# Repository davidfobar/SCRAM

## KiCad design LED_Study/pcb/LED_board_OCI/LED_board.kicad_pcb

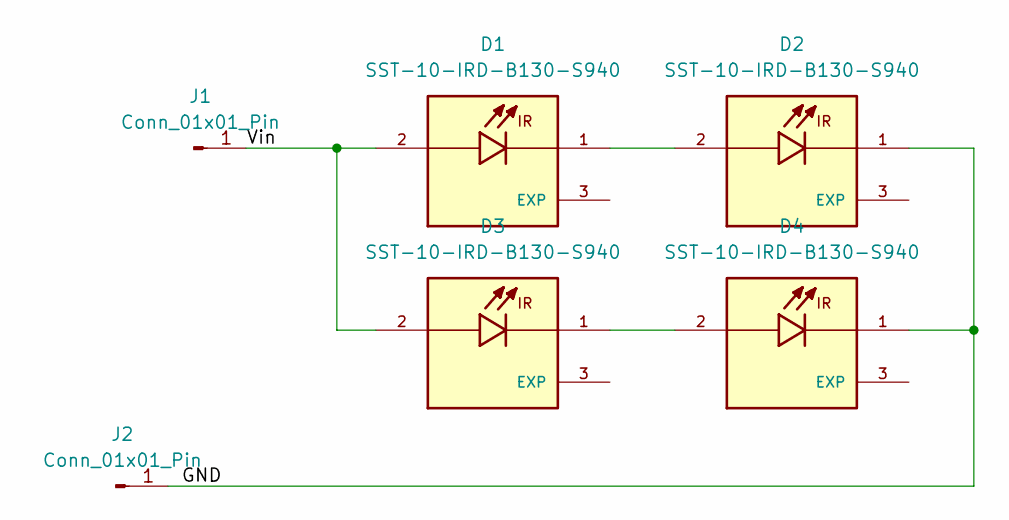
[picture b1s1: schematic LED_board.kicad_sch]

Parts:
D1, D2, D3, D4: SST-10-IRD-B130-S940; OCI-490; PARTREV 01
J1, J2: Conn_01x01_Pin; PinHeader_1x01_P1.00mm_Vertical

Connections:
/GND: D2.1, D4.1, J2.1
/Vin: D1.2, D3.2, J1.1
unnamed: D1.1, D2.2
unnamed: D3.1, D4.2

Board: 2 copper layers, 6 parts (0 on the bottom side), 4 nets, no tracks yet.

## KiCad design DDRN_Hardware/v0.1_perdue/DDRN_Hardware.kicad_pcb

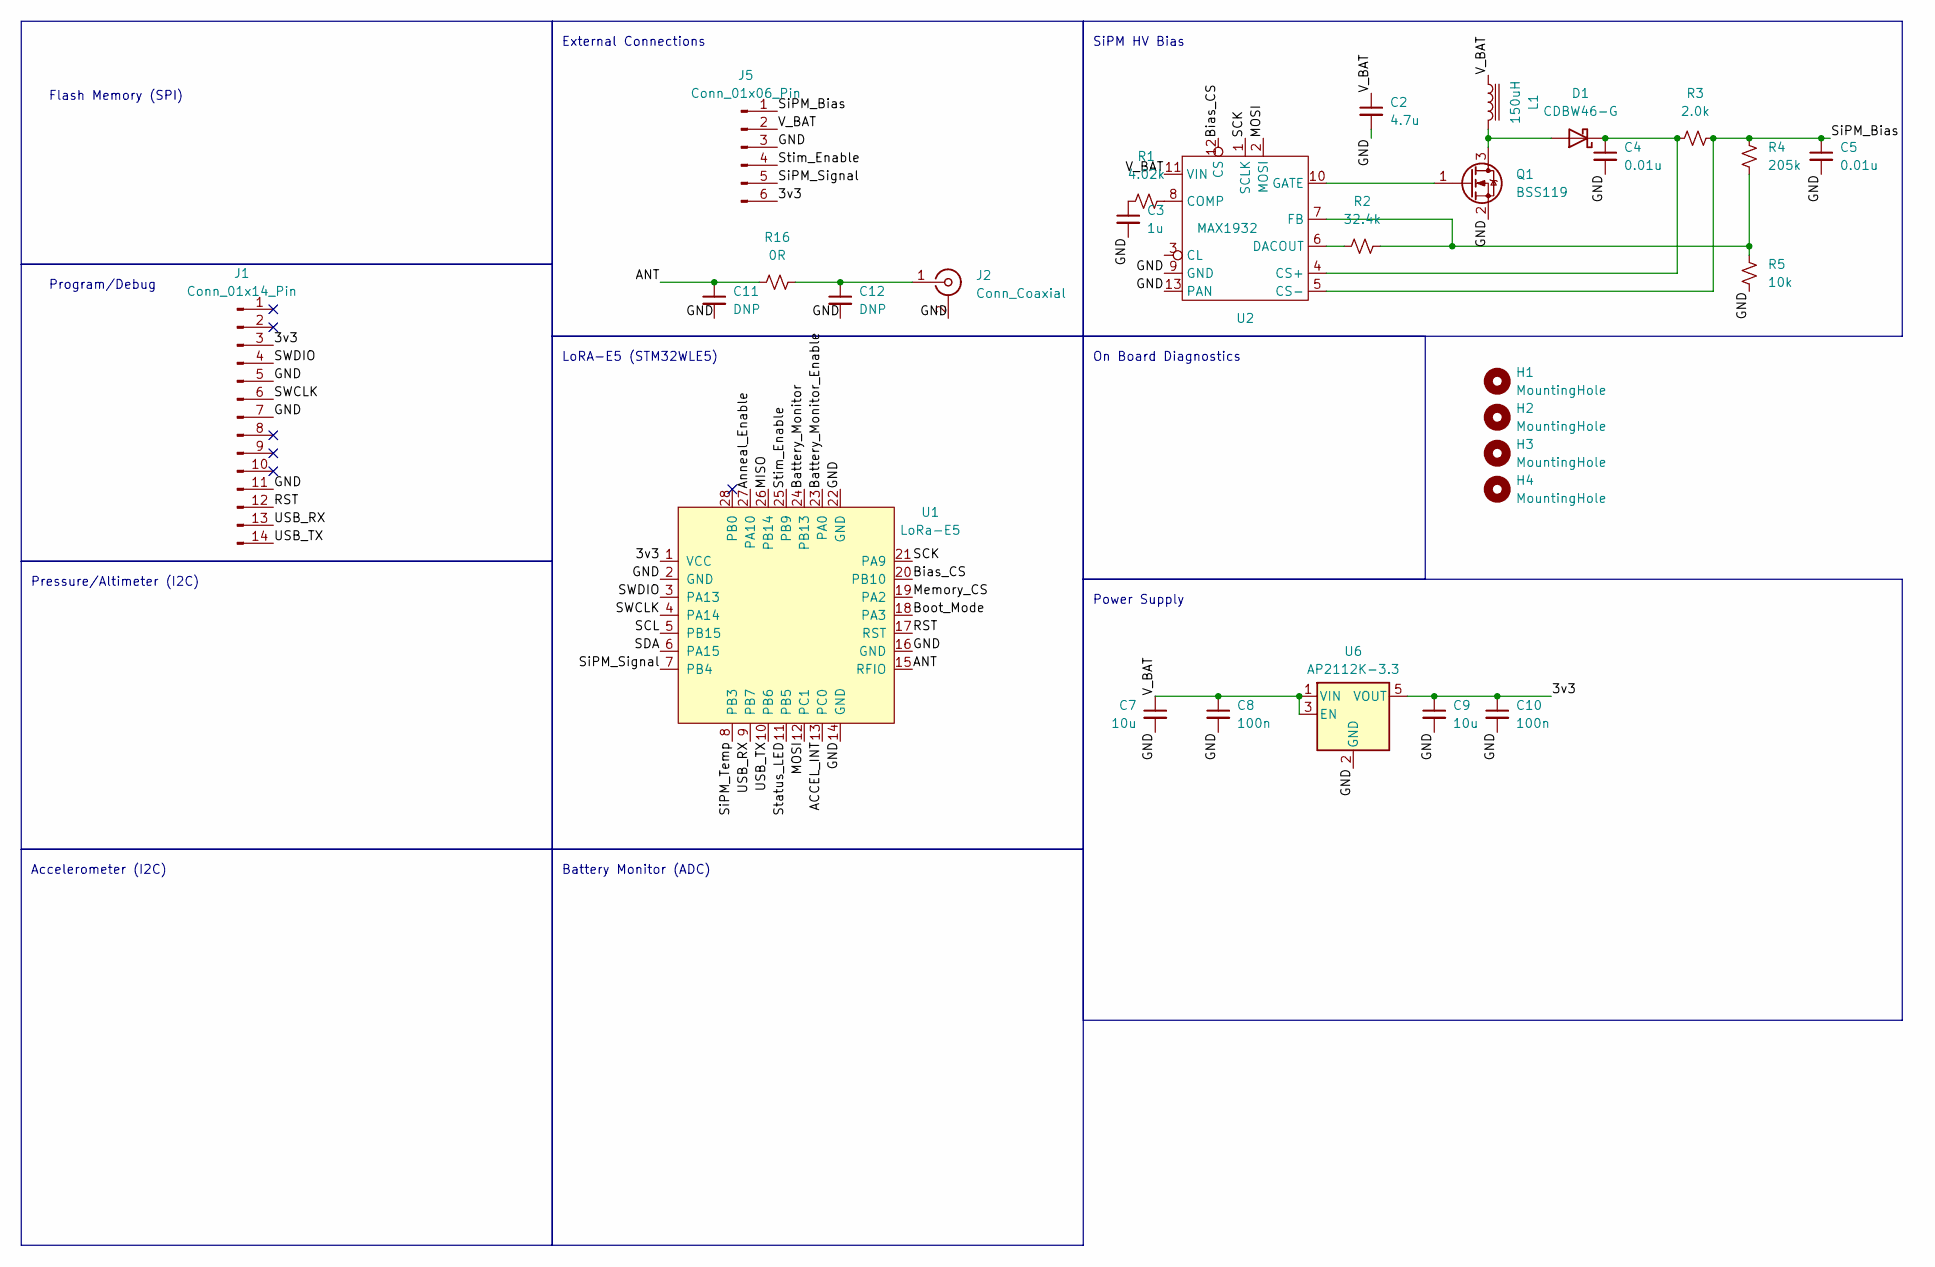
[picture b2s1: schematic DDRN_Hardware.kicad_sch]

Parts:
C2: 4.7u; C_0805_2012Metric_Pad1.18x1.45mm_HandSolder
C3: 1u; C_0805_2012Metric_Pad1.18x1.45mm_HandSolder
C4, C5: 0.01u; C_0805_2012Metric_Pad1.18x1.45mm_HandSolder
C7, C9: 10u; C_0805_2012Metric_Pad1.18x1.45mm_HandSolder
C8, C10: 100n; C_0805_2012Metric_Pad1.18x1.45mm_HandSolder
C11, C12: DNP; C_0805_2012Metric_Pad1.18x1.45mm_HandSolder
D1: CDBW46-G; D_SOD-123
H1, H2, H3, H4: MountingHole; MountingHole_3.2mm_M3_DIN965
J1: Conn_01x14_Pin; Tag-Connect_TC2070-IDC-FP_2x07_P1.27mm_Vertical
J2: Conn_Coaxial; U.FL_Hirose_U.FL-R-SMT-1_Vertical
J5: Conn_01x06_Pin; Tag-Connect_TC2030-IDC-FP_2x03_P1.27mm_Vertical
L1: 150uH; SRN4026
Q1: BSS119; SOT-23
R1: 4.02k; R_0805_2012Metric_Pad1.20x1.40mm_HandSolder
R2: 32.4k; R_0805_2012Metric_Pad1.20x1.40mm_HandSolder
R3: 2.0k; R_0805_2012Metric_Pad1.20x1.40mm_HandSolder
R4: 205k; R_0805_2012Metric_Pad1.20x1.40mm_HandSolder
R5: 10k; R_0805_2012Metric_Pad1.20x1.40mm_HandSolder
R16: 0R; R_0805_2012Metric_Pad1.20x1.40mm_HandSolder
U1: LoRa-E5
U2: MAX1932; MAX1932_handsolder
U6: AP2112K-3.3; SOT-23-5

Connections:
/3v3: C9.1, C10.1, J1.3, J5.6, U1.1 (VCC), U6.5 (VOUT)
/ACCEL_INT: U1.13 (PC0)
/ANT: C11.1, R16.2, U1.15 (RFIO)
/Anneal_Enable: U1.27 (PA10)
/Battery_Monitor: U1.24 (PB13~)
/Battery_Monitor_Enable: U1.23 (PA0)
/Bias_CS: U1.20 (PB10), U2.12 (CS)
/Boot_Mode: U1.18 (PA3)
/GND: C2.2, C3.2, C4.2, C5.2, C7.2, C8.2, C9.2, C10.2, C11.2, C12.2, J1.5, J1.7, J1.11, J2.2 (Ext), J5.3, Q1.2 (S), R5.2, U1.2 (GND), U1.14 (GND), U1.16 (GND), U1.22 (GND), U2.9 (GND), U2.13 (PAN), U6.2 (GND)
/MISO: U1.26 (PB14)
/MOSI: U1.12 (PC1), U2.2 (MOSI)
/Memory_CS: U1.19 (PA2)
/RST: J1.12, U1.17 (RST)
/SCK: U1.21 (PA9), U2.1 (SCLK)
/SCL: U1.5 (PB15)
/SDA: U1.6 (PA15)
/SWCLK: J1.6, U1.4 (PA14)
/SWDIO: J1.4, U1.3 (PA13)
/SiPM_Bias: C5.1, J5.1, R3.2, R4.1, U2.5 (CS-)
/SiPM_Signal: J5.5, U1.7 (PB4)
/SiPM_Temp: U1.8 (PB3)
/Status_LED: U1.11 (PB5)
/Stim_Enable: J5.4, U1.25 (PB9)
/USB_RX: J1.13, U1.9 (PB7)
/USB_TX: J1.14, U1.10 (PB6)
/V_BAT: C2.1, C7.1, C8.1, J5.2, L1.1, U2.11 (VIN), U6.1 (VIN), U6.3 (EN)
unnamed: C3.1, R1.1
unnamed: D1.2 (A), L1.2, Q1.3 (D)
unnamed: C4.1, D1.1 (K), R3.1, U2.4 (CS+)
unnamed: C12.1, J2.1 (In), R16.1
unnamed: Q1.1 (G), U2.10 (GATE)
unnamed: R1.2, U2.8 (COMP)
unnamed: R2.1, U2.6 (DACOUT)
unnamed: R2.2, R4.2, R5.1, U2.7 (FB)

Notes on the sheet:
Power Supply
Pressure/Altimeter (I2C)
Accelerometer (I2C)
On Board Diagnostics
Flash Memory (SPI)
External Connections
SiPM HV Bias
Program/Debug
LoRA-E5 (STM32WLE5)
Battery Monitor (ADC)

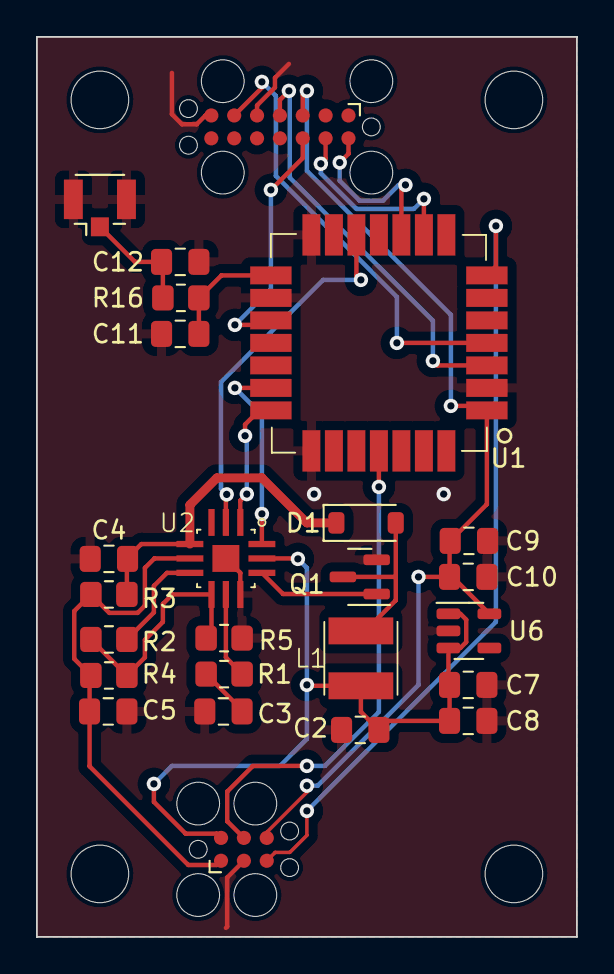
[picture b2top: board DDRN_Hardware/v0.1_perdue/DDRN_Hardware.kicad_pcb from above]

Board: 2 copper layers, 30.0 x 50.0 mm, 29 parts (0 on the bottom side), 23 nets.

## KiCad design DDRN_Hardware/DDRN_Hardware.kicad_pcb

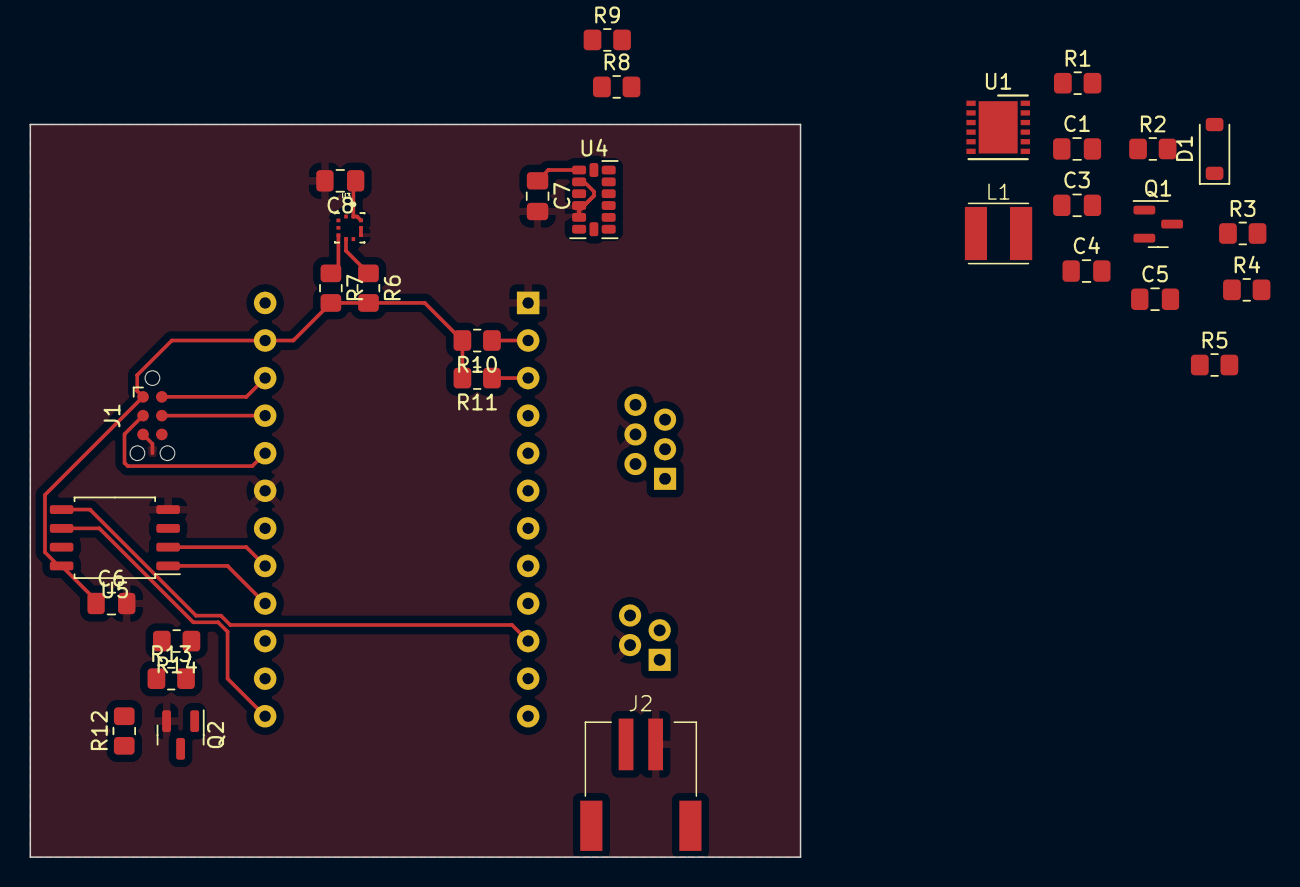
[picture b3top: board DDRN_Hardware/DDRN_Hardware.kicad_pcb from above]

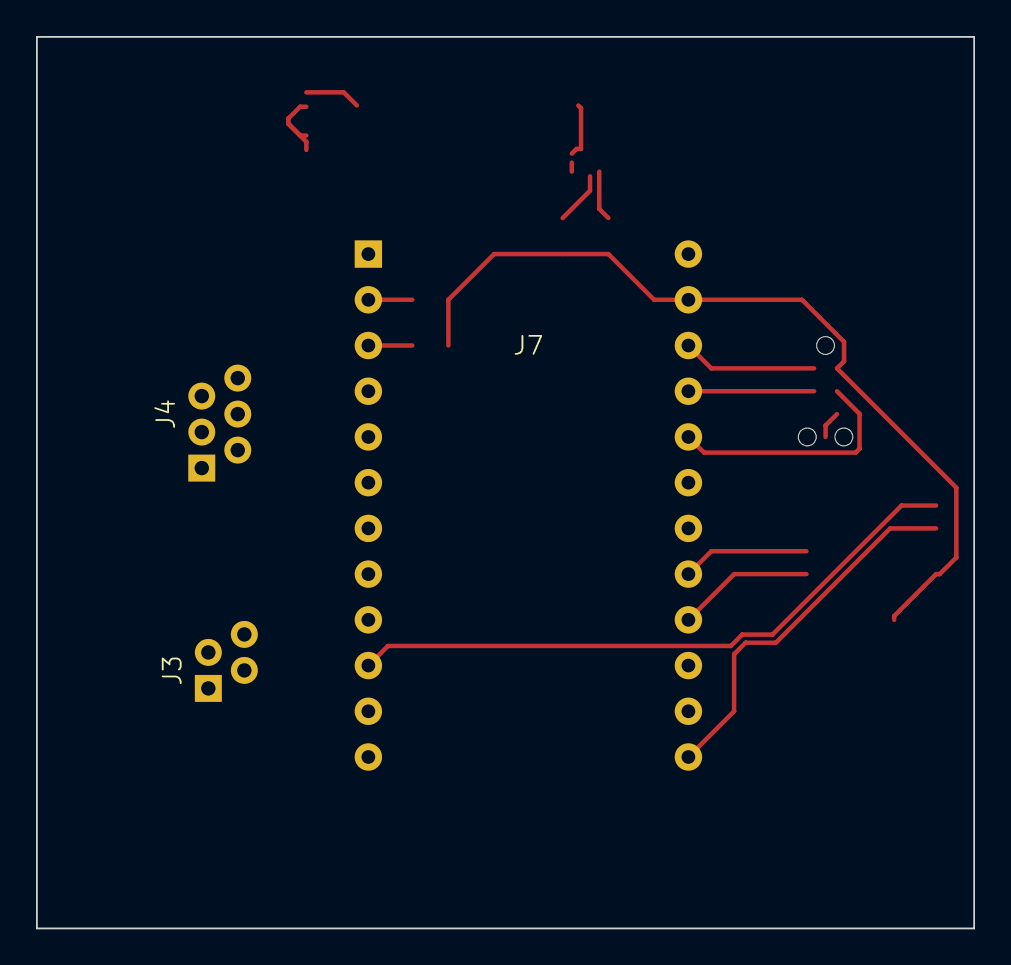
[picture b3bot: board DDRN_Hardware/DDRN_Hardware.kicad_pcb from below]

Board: 2 copper layers, 52.1 x 49.5 mm, 34 parts (3 on the bottom side), 34 nets.

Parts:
C1: 4.7u; C_0805_2012Metric_Pad1.18x1.45mm_HandSolder
C3, C6, C7, C8: 1u; C_0805_2012Metric_Pad1.18x1.45mm_HandSolder
C4, C5: 0.01u; C_0805_2012Metric_Pad1.18x1.45mm_HandSolder
D1: CDBW46-G; D_SOD-123
J1: SWD; Tag-Connect_TC2030-IDC-NL_2x03_P1.27mm_Vertical
J2: Conn_01x02_Pin; JST-PH-RH-SM
J3: Conn_01x04_Pin; SLW4S-1C7LF
J4: Conn_01x06_Pin; SLW6S-1C7LF
J7: Conn_02x12_Counter_Clockwise; E5-mini-dev
L1: 150uH; SRN4026
Q1, Q2: BSS119; SOT-23
R1: 4.02k; R_0805_2012Metric_Pad1.20x1.40mm_HandSolder
R2: 32.4k; R_0805_2012Metric_Pad1.20x1.40mm_HandSolder
R3: 2.0k; R_0805_2012Metric_Pad1.20x1.40mm_HandSolder
R4: 205k; R_0805_2012Metric_Pad1.20x1.40mm_HandSolder
R5, R6, R7, R8, R9, R12, R13: 10k; R_0805_2012Metric_Pad1.20x1.40mm_HandSolder
R10, R11: 4.7k; R_0805_2012Metric_Pad1.20x1.40mm_HandSolder
R14: 100; R_0805_2012Metric_Pad1.20x1.40mm_HandSolder
U1: MAX1932; DFN-12-1EP_4x4mm_P0.65mm_EP2.64x3.54mm
U3: BMP390L; XDCR_BMP390L
U4: ADXL343; LGA-14_3x5mm_P0.8mm_LayoutBorder1x6y
U5: W25Q32JVSS; SOIC-8_5.23x5.23mm_P1.27mm

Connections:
/3v3: C1.1, C6.1, C7.1, C8.1, J1.1 (VCC), J4.1, J7.23, R6.2, R7.2, R9.2, R10.2, R11.2, U3.1 (VDDIO), U3.10 (VDD), U4.1 (Vdd_I/O), U4.6 (Vs), U5.8 (VCC)
/ACCEL_INT: J7.9, U4.8 (INT1)
/Anneal_Enable: J3.4, J7.8
/Battery_Monitor: J7.15, R14.1
/Battery_Monitor_Enable: J7.14, Q2.1 (G)
/Bias_CS: J7.18, U1.12 (CS)
/MISO: J7.17, U5.2 (DO(IO1))
/MOSI: J7.10, U1.2 (MOSI), U5.5 (DI(IO0))
/Memory_CS: J7.16, U5.1 (~CS)
/RST: J1.3 (~RESET), J7.20
/SCK: J7.13, U1.1 (SCLK), U5.6 (CLK)
/SCL: J7.2, R10.1, U3.2 (SCK/SCL), U4.14 (SCL/SCLK)
/SDA: J7.3, R11.1, U3.4 (SDI/SDO/SDA), U4.13 (SDA/SDI/SDIO)
/SWCLK: J1.4 (SWCLK), J7.21
/SWDIO: J1.2 (SWDIO), J7.22
/SiPM_Bias: C5.1, J4.3, R3.2, R4.1, U1.5 (CS-)
/SiPM_Signal: J4.5, J7.4
/SiPM_Temp: J4.2, J7.5
/Stim_Enable: J3.3, J7.12
/V_BAT: J2.1, J3.1, J4.6, L1.1, R12.1, U1.11 (VIN)
GND: C1.2, C3.2, C4.2, C5.2, C6.2, C7.2, C8.2, J1.5 (GND), J2.2, J3.2, J4.4, J7.1, J7.19, Q1.2 (S), Q2.2 (S), R5.2, R8.2, U1.9 (GND), U1.13 (PAN), U3.3 (VSS/GND), U3.8 (VSS/GND), U3.9 (VSS/GND), U4.2 (GND), U4.4 (GND), U4.5 (GND), U5.4 (GND)
unnamed: C3.1, R1.1
unnamed: D1.2 (A), L1.2, Q1.3 (D)
unnamed: C4.1, D1.1 (K), R3.1, U1.4 (CS+)
unnamed: Q1.1 (G), U1.10 (GATE)
unnamed: Q2.3 (D), R13.2
unnamed: R12.2, R13.1, R14.2
unnamed: R1.2, U1.8 (COMP)
unnamed: R2.1, U1.6 (DACOUT)
unnamed: R2.2, R4.2, R5.1, U1.7 (FB)
unnamed: R7.1, U3.5 (SDO/DNC/SA0)
unnamed: R6.1, U3.6 (~CS)
unnamed: R8.1, U4.12 (SDO/ADDR)
unnamed: R9.1, U4.7 (~CS)

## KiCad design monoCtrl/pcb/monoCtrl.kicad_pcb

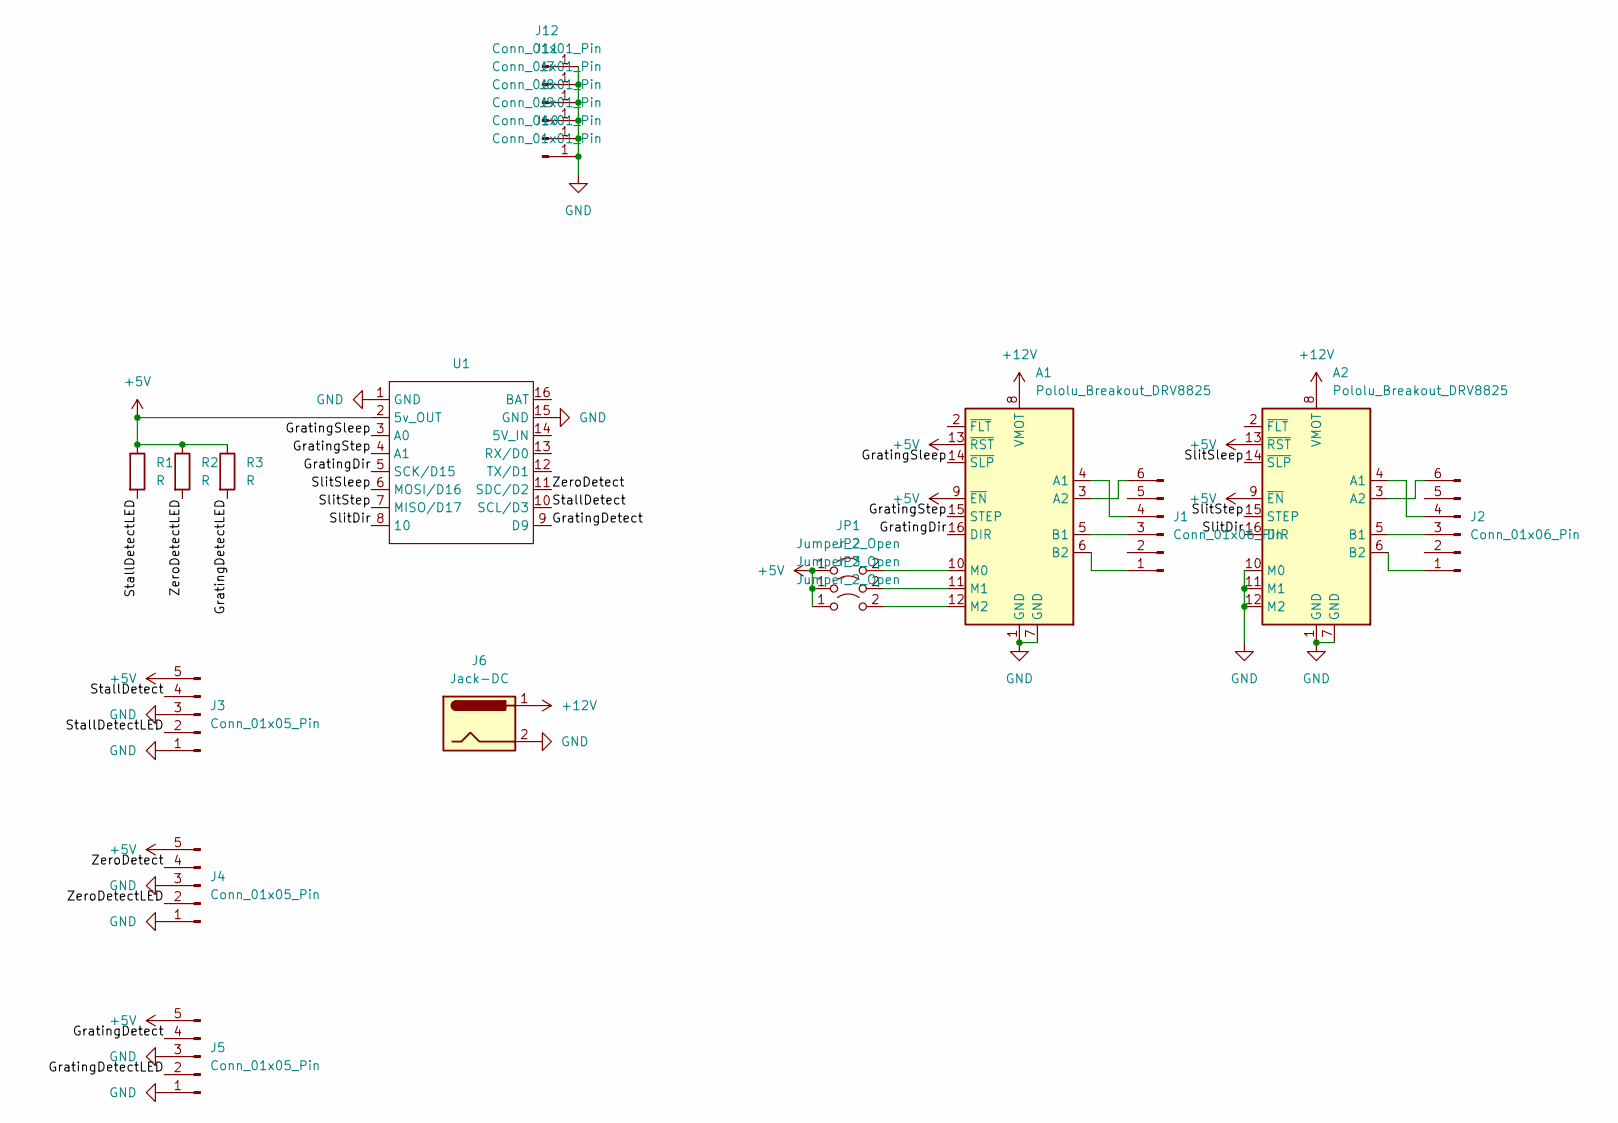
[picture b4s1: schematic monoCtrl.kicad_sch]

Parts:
A1, A2: Pololu_Breakout_DRV8825; Pololu_Breakout-16_15.2x20.3mm
J1, J2: Conn_01x06_Pin; 1x06_BoardEdge
J3, J4, J5: Conn_01x05_Pin; 1x05_BoardEdge
J6: Jack-DC; power
J7, J8, J9, J10, J11, J12: Conn_01x01_Pin; air jump
JP1, JP2, JP3: Jumper_2_Open; SolderJumper-2_P1.3mm_Open_TrianglePad1.0x1.5mm
R1, R2, R3: R; R_0805_2012Metric
U1: Beetle_CM-32U4

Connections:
+5V: A1.9 (~EN), A1.13 (~RST), A2.9 (~EN), A2.13 (~RST), J3.5, J4.5, J5.5, JP1.1 (A), JP2.1 (A), JP3.1 (A), R1.1, R2.1, R3.1, U1.2 (5v_OUT)
+12V: A1.8 (VMOT), A2.8 (VMOT), J6.1
/GratingDetect: J5.4, U1.9 (D9)
/GratingDetectLED: J5.2, R3.2
/GratingDir: A1.16 (DIR), U1.5 (SCK/D15)
/GratingSleep: A1.14 (~SLP), U1.3 (A0)
/GratingStep: A1.15 (STEP), U1.4 (A1)
/SlitDir: A2.16 (DIR), U1.8 (10)
/SlitSleep: A2.14 (~SLP), U1.6 (MOSI/D16)
/SlitStep: A2.15 (STEP), U1.7 (MISO/D17)
/StallDetect: J3.4, U1.10 (SCL/D3)
/StallDetectLED: J3.2, R1.2
/ZeroDetect: J4.4, U1.11 (SDC/D2)
/ZeroDetectLED: J4.2, R2.2
GND: A1.1 (GND), A1.7 (GND), A2.1 (GND), A2.7 (GND), A2.10 (M0), A2.11 (M1), A2.12 (M2), J3.1, J3.3, J4.1, J4.3, J5.1, J5.3, J6.2, J7.1, J8.1, J9.1, J10.1, J11.1, J12.1, U1.1 (GND), U1.15 (GND)
unnamed: A1.4 (A1), J1.4
unnamed: A1.3 (A2), J1.6
unnamed: A1.5 (B1), J1.3
unnamed: A1.6 (B2), J1.1
unnamed: A1.10 (M0), JP1.2 (B)
unnamed: A1.11 (M1), JP2.2 (B)
unnamed: A1.12 (M2), JP3.2 (B)
unnamed: A2.4 (A1), J2.4
unnamed: A2.3 (A2), J2.6
unnamed: A2.5 (B1), J2.3
unnamed: A2.6 (B2), J2.1

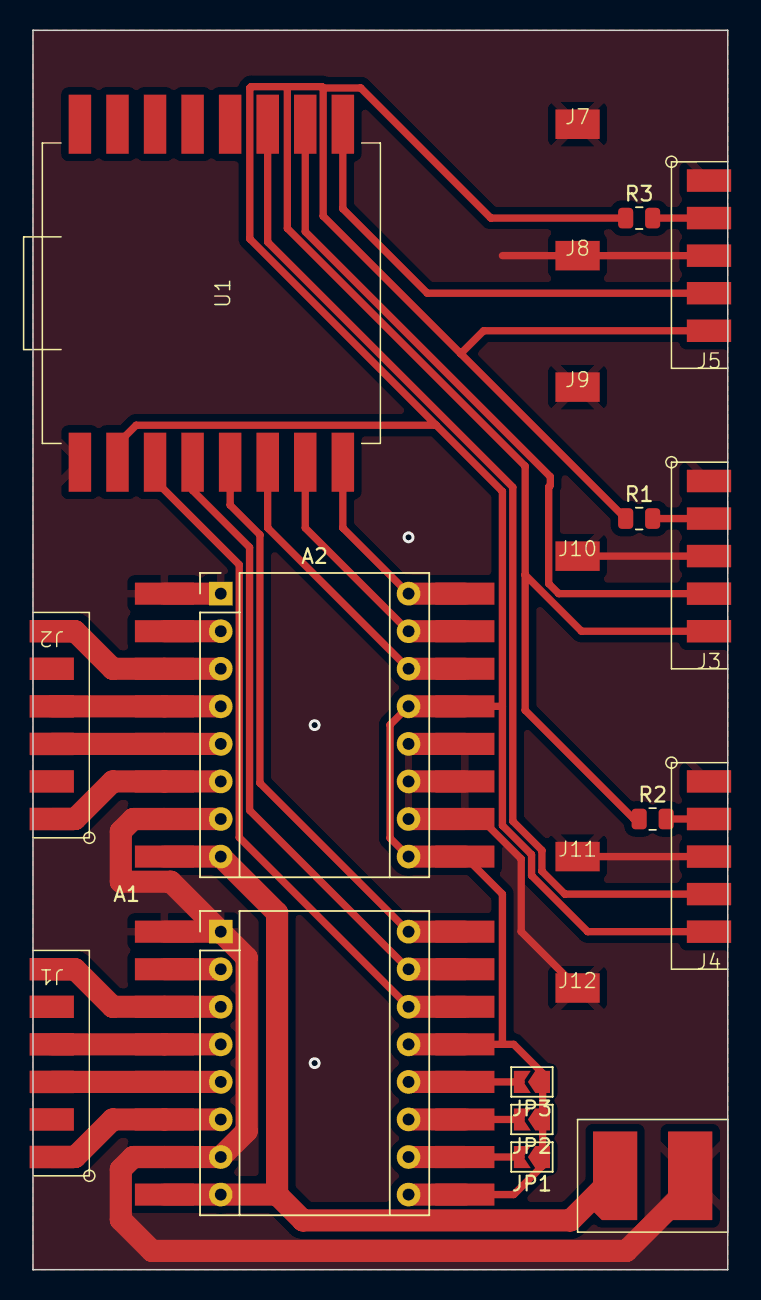
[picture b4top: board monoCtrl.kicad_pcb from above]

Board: 2 copper layers, 47.0 x 83.8 mm, 21 parts (0 on the bottom side), 26 nets.

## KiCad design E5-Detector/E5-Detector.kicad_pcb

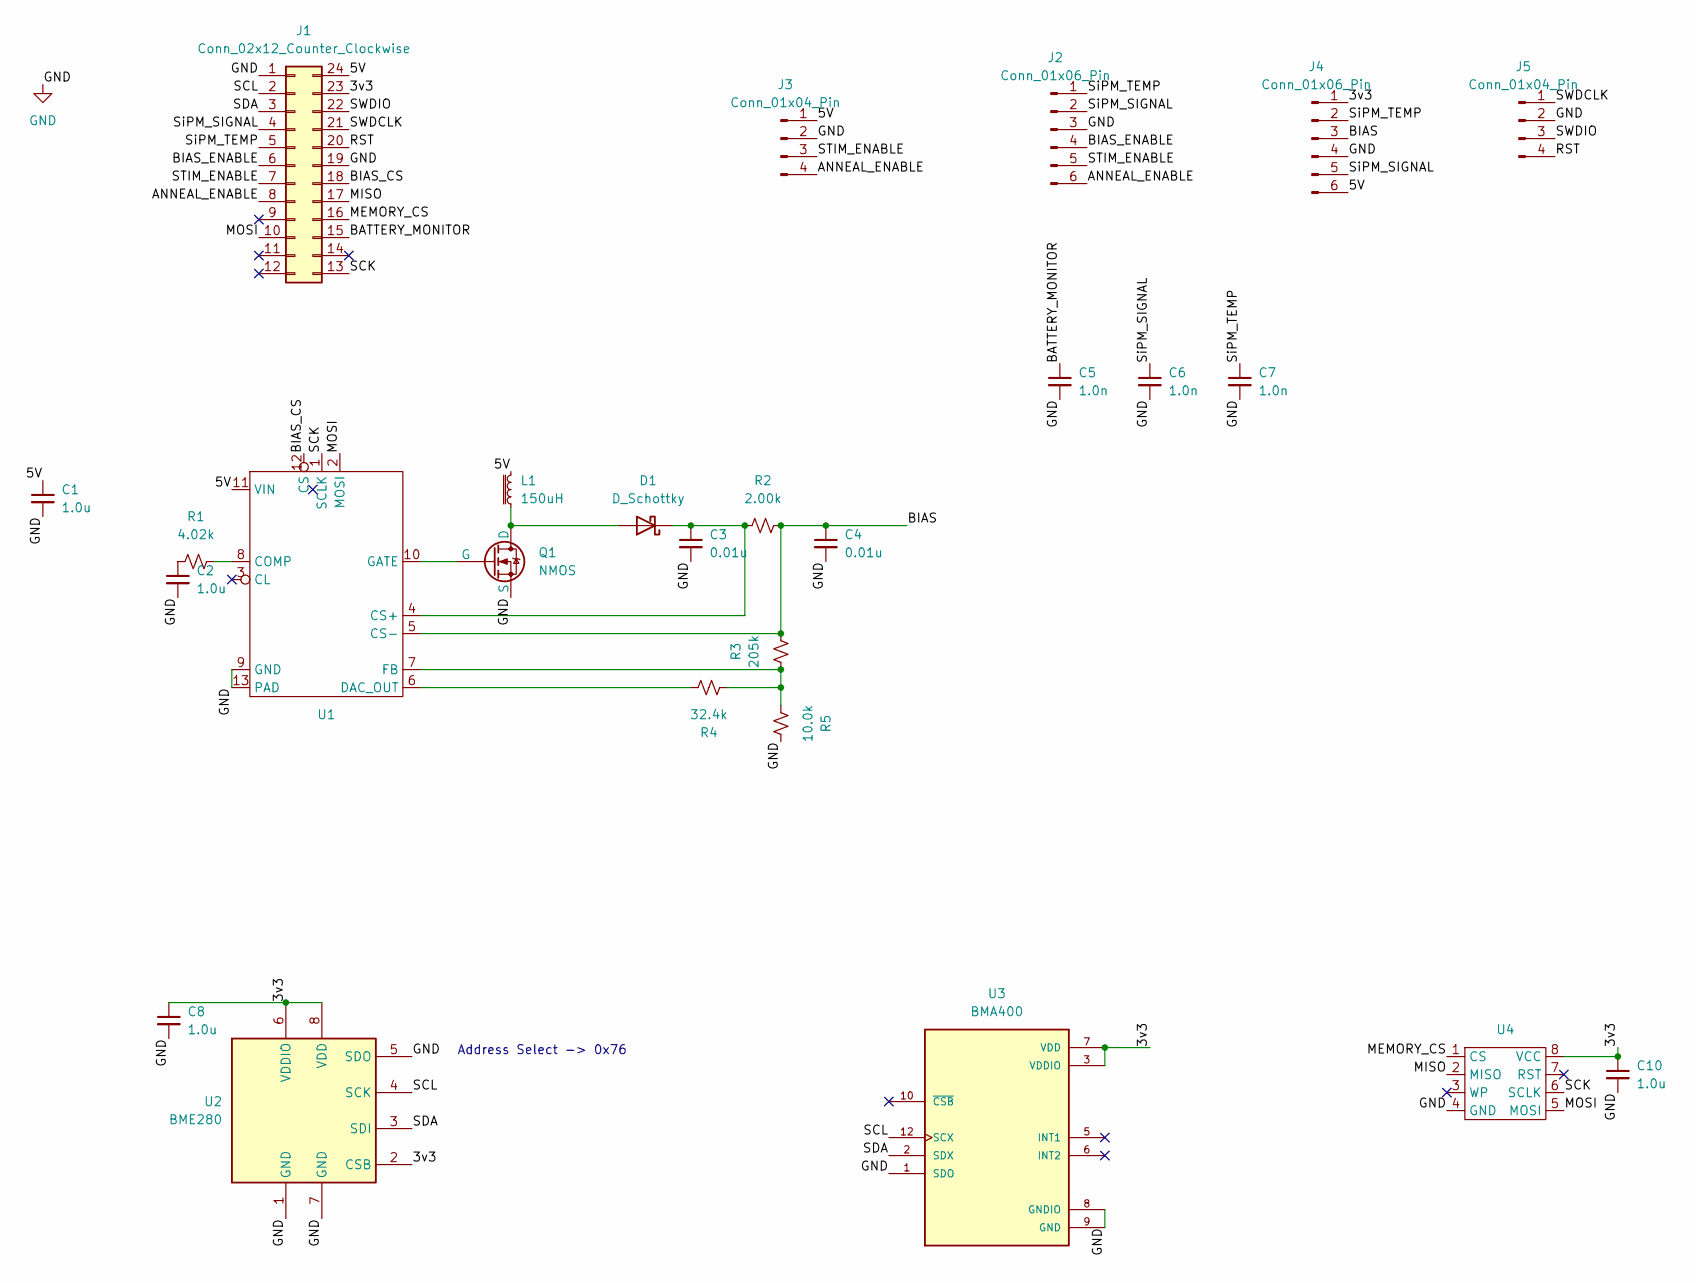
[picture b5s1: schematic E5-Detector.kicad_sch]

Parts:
C1, C2, C8, C10: 1.0u; C_0805_2012Metric_Pad1.18x1.45mm_HandSolder
C3, C4: 0.01u; C_0805_2012Metric_Pad1.18x1.45mm_HandSolder
C5, C6, C7: 1.0n; C_0805_2012Metric_Pad1.18x1.45mm_HandSolder
D1: D_Schottky; D_0805_2012Metric_Pad1.15x1.40mm_HandSolder
J1: Conn_02x12_Counter_Clockwise; E5-mini
J2, J4: Conn_01x06_Pin; PinHeader_1x06_P2.54mm_Vertical
J3, J5: Conn_01x04_Pin; PinHeader_1x04_P2.54mm_Vertical
L1: 150uH; L_Coilcraft_XAL4020-XXX
Q1: NMOS; SOT-23_Handsoldering
R1: 4.02k; R_0805_2012Metric_Pad1.20x1.40mm_HandSolder
R2: 2.00k; R_0805_2012Metric_Pad1.20x1.40mm_HandSolder
R3: 205k; R_0805_2012Metric_Pad1.20x1.40mm_HandSolder
R4: 32.4k; R_0805_2012Metric_Pad1.20x1.40mm_HandSolder
R5: 10.0k; R_0805_2012Metric_Pad1.20x1.40mm_HandSolder
U1: DFN-12-1EP_4x4mm_P0.65mm_EP2.64x3.54mm
U2: BME280; Bosch_LGA-8_2.5x2.5mm_P0.65mm_ClockwisePinNumbering
U3: BMA400; XDCR_BMA400
U4: SOIC-8_5.23x5.23mm_P1.27mm

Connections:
/3v3: C8.1, C10.1, J1.23, J4.1, U2.2 (CSB), U2.6 (VDDIO), U2.8 (VDD), U3.3 (VDDIO), U3.7 (VDD), U4.8 (VCC)
/5V: C1.1, J1.24, J3.1, J4.6, L1.2, U1.11 (VIN)
/ANNEAL_ENABLE: J1.8, J2.6, J3.4
/BATTERY_MONITOR: C5.1, J1.15
/BIAS: C4.1, J4.3, R2.2, R3.2, U1.5 (CS-)
/BIAS_CS: J1.18, U1.12 (CS)
/BIAS_ENABLE: J1.6, J2.4
/MEMORY_CS: J1.16, U4.1 (CS)
/MISO: J1.17, U4.2 (MISO)
/MOSI: J1.10, U1.2 (MOSI), U4.5 (MOSI)
/RST: J1.20, J5.4
/SCK: J1.13, U1.1 (SCLK), U4.6 (SCLK)
/SCL: J1.2, U2.4 (SCK), U3.12 (SCX)
/SDA: J1.3, U2.3 (SDI), U3.2 (SDX)
/STIM_ENABLE: J1.7, J2.5, J3.3
/SWDCLK: J1.21, J5.1
/SWDIO: J1.22, J5.3
/SiPM_SIGNAL: C6.1, J1.4, J2.2, J4.5
/SiPM_TEMP: C7.1, J1.5, J2.1, J4.2
GND: C1.2, C2.2, C3.2, C4.2, C5.2, C6.2, C7.2, C8.2, C10.2, J1.1, J1.19, J2.3, J3.2, J4.4, J5.2, Q1.3 (S), R5.2, U1.9 (GND), U1.13 (PAD), U2.1 (GND), U2.5 (SDO), U2.7 (GND), U3.1 (SDO), U3.8 (GNDIO), U3.9 (GND), U4.4 (GND)
unnamed: C2.1, R1.1
unnamed: D1.2 (A), L1.1, Q1.1 (D)
unnamed: C3.1, D1.1 (K), R2.1, U1.4 (CS+)
unnamed: Q1.2 (G), U1.10 (GATE)
unnamed: R1.2, U1.8 (COMP)
unnamed: R4.2, U1.6 (DAC_OUT)
unnamed: R3.1, R4.1, R5.1, U1.7 (FB)

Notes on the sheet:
Address Select -> 0x76

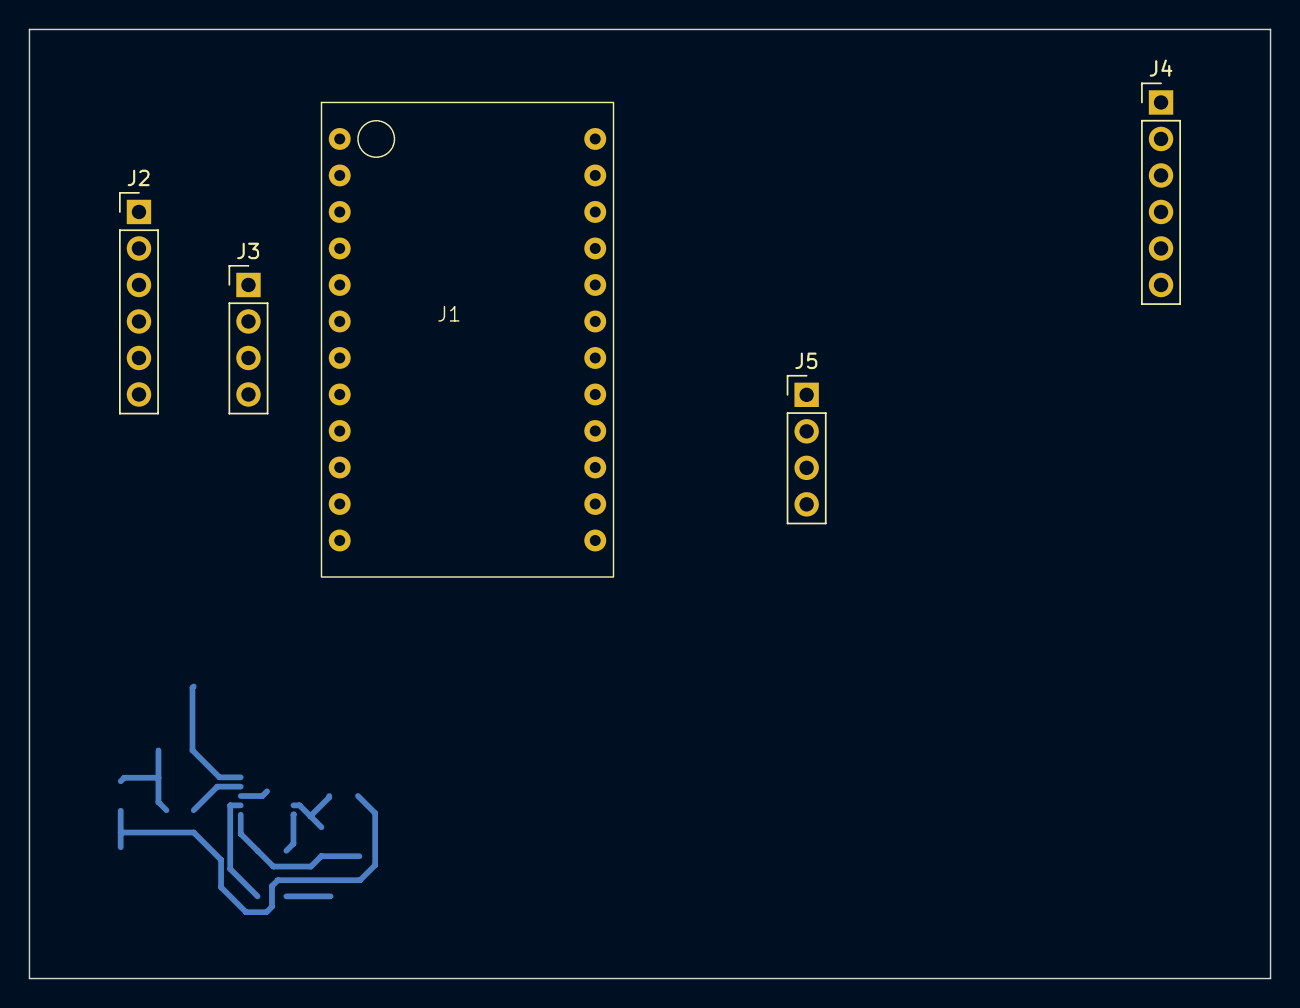
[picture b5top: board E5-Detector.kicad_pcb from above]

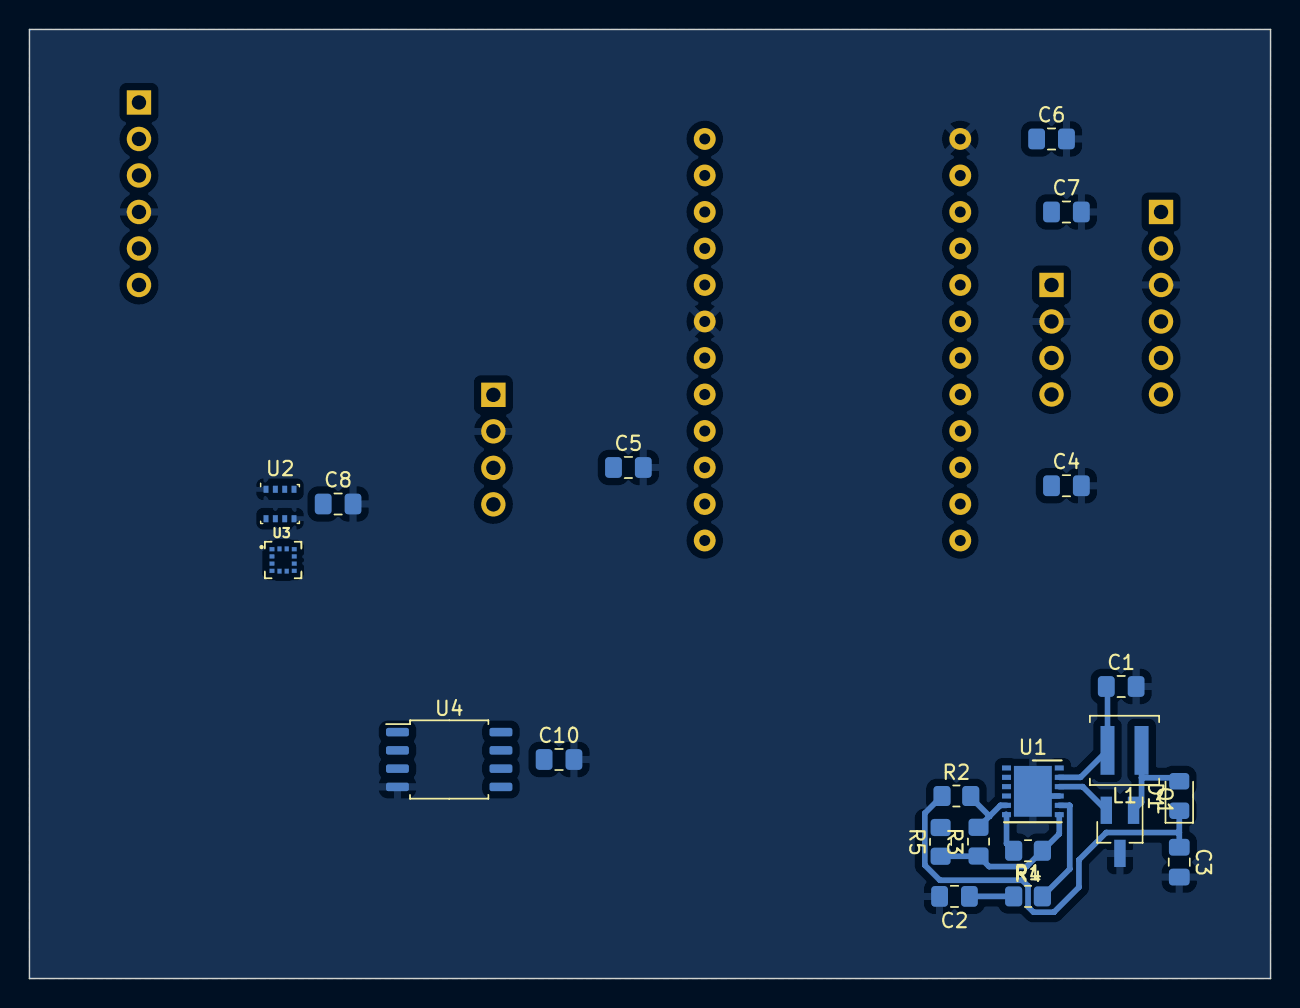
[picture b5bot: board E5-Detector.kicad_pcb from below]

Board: 2 copper layers, 86.4 x 66.0 mm, 26 parts (21 on the bottom side), 27 nets.

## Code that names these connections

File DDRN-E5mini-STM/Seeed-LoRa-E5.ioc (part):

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Mcu.Name=STM32WLE5JCIx
Mcu.Package=UFBGA73
Mcu.UserName=STM32WLE5JCIx
PA0.GPIOParameters=GPIO_Label
PA0.GPIO_Label=Env_Sens_Enable
PA0.Signal=GPIO_Output
PA10.GPIOParameters=GPIO_Label
PA10.GPIO_Label=Anneal_Enable
PA10.Signal=GPIO_Output
PA13.Mode=Serial_Wire
PA13.Signal=DEBUG_JTMS-SWDIO
PA14.Mode=Serial_Wire
PA14.Signal=DEBUG_JTCK-SWCLK
PA15.Mode=I2C
PA15.Signal=I2C2_SDA
PA2.GPIOParameters=GPIO_Label
PA2.GPIO_Label=Memory_CS
PA2.Signal=GPIO_Output
PA3.GPIOParameters=GPIO_Label
PA3.GPIO_Label=Boot_Mode
PA3.Signal=GPIO_Input
PA4.GPIOParameters=GPIO_Speed,GPIO_Label
PA4.GPIO_Label=RF_CTRL1
PA4.GPIO_Speed=GPIO_SPEED_FREQ_VERY_HIGH
PA4.Signal=GPIO_Output
PA5.GPIOParameters=GPIO_Speed,GPIO_Label
PA5.GPIO_Label=RF_CTRL2
PA5.GPIO_Speed=GPIO_SPEED_FREQ_VERY_HIGH
PA5.Signal=GPIO_Output
PA9.Mode=Full_Duplex_Master
PA9.Signal=SPI2_SCK
PB0-VDD_TCXO.Mode=HSE-TCXO
PB0-VDD_TCXO.Signal=VDDTCXO
PB10.GPIOParameters=GPIO_Label
PB10.GPIO_Label=Bias_CS
PB10.Signal=GPIO_Output
PB13.GPIOParameters=GPIO_Label
PB13.GPIO_Label=Battery_Monitor
PB13.Mode=IN0
PB13.Signal=ADC_IN0
PB14.Mode=Full_Duplex_Master
PB14.Signal=SPI2_MISO
PB15.Mode=I2C
PB15.Signal=I2C2_SCL
PB3.GPIOParameters=GPIO_Label
PB3.GPIO_Label=SiPM_Temp
PB3.Mode=IN2
PB3.Signal=ADC_IN2
PB4.GPIOParameters=GPIO_Label
PB4.GPIO_Label=SiPM_Signal
PB4.Mode=IN3
PB4.Signal=ADC_IN3
PB5.GPIOParameters=GPIO_Speed,PinState,GPIO_Label
PB5.GPIO_Label=LED2
PB5.GPIO_Speed=GPIO_SPEED_FREQ_VERY_HIGH
PB5.PinState=GPIO_PIN_SET
PB5.Signal=GPIO_Output
PB6.GPIOParameters=GPIO_Speed,GPIO_Label
PB6.GPIO_Label=USARTx_TX
PB6.GPIO_Speed=GPIO_SPEED_FREQ_VERY_HIGH
PB6.Mode=Asynchronous
PB6.Signal=USART1_TX
PB7.GPIOParameters=GPIO_Speed,GPIO_Label
PB7.GPIO_Label=USARTx_RX
PB7.GPIO_Speed=GPIO_SPEED_FREQ_VERY_HIGH
PB7.Mode=Asynchronous
PB7.Signal=USART1_RX
PB9.GPIOParameters=GPIO_Label
PB9.GPIO_Label=Stim_Enable
PB9.Signal=GPIO_Output
PC0.GPIOParameters=GPIO_Label
PC0.GPIO_Label=Accel_Int
PC0.Signal=GPXTI0
PC1.Mode=Full_Duplex_Master
PC1.Signal=SPI2_MOSI
PC14-OSC32_IN.Mode=LSE-External-Oscillator
PC14-OSC32_IN.Signal=RCC_OSC32_IN
PC15-OSC32_OUT.Mode=LSE-External-Oscillator
PC15-OSC32_OUT.Signal=RCC_OSC32_OUT
RCC.HSE_VALUE=32000000
RCC.SYSCLKFreq_VALUE=48000000
board=custom

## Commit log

2023-09-14 added monochromator controller initial design files
2023-09-14 finished v0.1
    ready to etch
2023-10-02 init commit
2023-10-02 pin assignments documented
2023-10-02 configured stm32cubeMX
2023-10-02 changed from EWARM to makefile
2023-10-02 proof of toolchain
2023-10-03 getting ready to confirm DIO
2023-10-03 I can now build using cmake - c++ for the win
2023-10-03 confirmed digitalIO functions
2023-10-03 3 analog channels function
2023-10-04 init
2023-10-04 rm radiolab
2023-10-04 first compile of seeec LoraWAN
2023-10-04 functional node code compiled
2023-10-04 corrected location information
2023-10-04 refreshed Seeed library
2023-10-04 removed uneccesary projects
2023-10-09 added chirpstack docker compsoe
2023-10-09 working cubeide project
2023-10-09 i got the keys to work
2023-10-09 move E5 folder
2023-10-09 added gpio and adc to .ioc file
2023-10-09 GPIO output function confirmed
2023-10-10 I can use all GPIO, adc is too slow
2023-10-10 removed old firmware project
2023-10-11 no change
2023-10-12 added monochrometer firmware to folder
2023-10-13 pcb work
2023-10-16 updated to chirpstack v4 and added sensors
2023-10-16 added detector pins
2023-10-16 added detector to main
2023-10-16 added default detector constructor
2023-10-16 added calibration curve to grating
2023-10-17 readData
2023-10-17 pcb design work
2023-10-17 pcb v1 work
2023-10-18 attempting STM on more time
2023-10-18 getting data back, but it is wrong
2023-10-18 changed delay function
2023-10-18 functional BMP390 code!
2023-10-19 working on LSM303
2023-10-19 troubleshooting LSM303
2023-10-19 renamed pio folder
2023-10-19 copied pin assignment file
2023-10-19 confirmed STM LoRaWAN
2023-10-19 updated kicad gitignore
2023-10-20 got LSM303_accel working
2023-10-20 kicad correction
2023-10-21 cleaning up the gitignore again
2023-10-21 prepare for merge
2023-10-21 added pin assignments to .ioc file
2023-10-22 pcb design reorganization
2023-10-22 v0.1 pcb complete?
2023-10-22 ordered pcb v.01
2023-10-28 moving files
2023-11-01 created exp mode
2023-11-01 90 percent solution for detector code - needs eval
2023-11-01 max1932 pin 1 fixed
2023-11-01 led board function verified
2023-11-02 fixed the batter monitor
2023-11-02 python
2023-11-02 added zip files to gitignore
2023-11-09 test
2023-11-09 added .zip
2023-11-29 testing upload
2023-11-30 xrs driver init
2023-12-20 added toggle red light
2024-01-16 added v0.1_perdue pcb
2024-01-18 led board design
2024-01-23 new boards
2024-01-23 added csz_cntr
2024-01-23 added testJAN
2024-01-23 Added python shell code of experiment
2024-01-23 Added python shell for experiment
2024-01-23 deleted testJAN
2024-01-24 updated boards and ordered from PCBway
2024-01-25 added x-ray generator class to shell
2024-01-25 Added variable names and called for user input.
2024-01-25 saved the file as a .ipynb
2024-01-26 changes in CSZ code
2024-01-26 moved to TCP/IP
2024-01-30 added manualStart
2024-02-06 preparing for experiment
2024-02-06 added remote terminal
2024-02-06 added code to detExp for numpy array
2024-02-08 added numpy
2024-02-08 CZT for numpy
2024-02-09 print
2024-02-15 working xray comms
2024-02-15 working xray comm
2024-02-15 xrs4 comms
2024-02-15 created communication with XRS4 with time delay
2024-02-15 added to automation in detExp
2024-02-21 created py file and started exp 2/21
2024-03-14 added tasks for dose exp at perdue
2024-03-14 added plotting method to detExp
2024-03-15 starting pytorch model
2024-03-15 proper decay over sample time
2024-03-15 kalman filter implemented
2024-03-15 det data filtered
2024-03-15 working on data structure
2024-03-16 created classes for field, det, gateways
2024-03-16 detector placement iwth uniform distrobution
2024-03-16 scattered detectors by arty and random gateway placement
2024-03-16 working on solving the system of equations
2024-03-16 got the dToF prediction to work
2024-03-17 working sim!
2024-03-17 functional gru model
2024-03-17 updated gitignore for sim npy files
2024-03-17 issues with the gru size
2024-03-17 functional training
2024-03-17 need to blur/smooth results
2024-03-18 functional convolutional reconstruction
2024-03-19 IdiotStick
2024-03-19 moved from upscale to fully connected
2024-04-22 fobar testing works
2024-07-18 Python Class to Run DELFIC
    ## Overview
    This code runs DELFIC at the command line and allows users to iterate over typical parameters that impact fallout distribution. It works by creating a class that contains the parameters and file loca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
    - Ensure DELFIC is installed and the FPRdriver.bat is edited following instructions below
    - User instantiates the DELFIC_input class with properties of the scenario (ex: input)
    - User can run DELFIC, which calls the 'run_delfic' function (ex: input.run_delfic()) which will:
    - Generate the input file in a subfolder of t
2024-07-23 py torch model
2024-07-23 pytorch model
2024-07-23 fixed puTorch model merge
2024-07-23 started multiprocessing on linux
2024-07-24 Update run_delfic_scripting.ipynb
    - Updated to run faster using different delfic cmd
    - Updated to exposure rate overlays for t=1 to t=24 hours after det
    - added logic to check OS
    - outputs in 3d array [t,x,y] dose val
    - saves output as .pkl file in input folder
    - removes delfic output files
2024-07-24 fixed linux processing
2024-07-24 - Added variability to winds - fixed input file to include all parameters
2024-07-24 staged changes
2024-07-26 plotting delfic results
2024-07-26 linregression
2024-07-29 used polar fit for detector deployment
2024-07-29 detector scattering functional
2024-07-29 callable DELFIC Data Generation
2024-07-30 working on getting the full sim to work
2024-07-30 got kalman filtering to work again
2024-08-01 got run time down significantly
2024-08-01 building large dataset overnight
2024-09-04 continued work to gen training data
2024-09-04 team work makes the dream work
2024-09-04 again
2024-09-08 LISAT Draft Edits
    - Added logic to generate plots for Sam's paper
    - Added a boolean in plotField to turn on/off the red line plotting
    - Added a sourceDirectory parameter to change folder to look for fallout fields for plotting Sam's fields
    - Added some windows specific logic to the dosimeter position and exp rate calcs.
2024-09-09 15 min time steps and GIF
    - Edited input file to output in 15 min time steps
    - Added code to make a gif of the decay of the field for those time steps
    - Uploaded a gif of the decay of a weapon at default input class parameters at time of commit.
2024-09-10 visualization
2024-09-10 reran delfic for 15 minute intervals and removed exponential curve fitting for detector response
2024-09-10 ready to train, need to solve env issue
2024-09-11 imporved location estimation performance
2024-10-01 model progress
